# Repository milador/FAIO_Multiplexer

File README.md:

# FAIO Multiplexer Switch 

FAIO Multiplexer is an open-source Assistive technology wing for Adafruit Feather boards which enables those with limited or no hand movement to use Adaptive switches as input to operate in multiple input modes.

FAIO Multiplexer USB supports following switch modes:

* Switch Access Mode ( HID Keyboard ) : Teal Led
* Morse Keyboard Mode ( HID Keyboard ) : Purple Led
* Morse Mouse Mode ( HID Mouse ) : Pink Led
* Settings Mode : Orange Led

FAIO Multiplexer Joystick supports following switch modes:

* Mode 1 (Button 1,Button 2,Button 3,Button 4) : Teal Led
* Mode 2 (Button 5,Button 6,Button 7,Button 8) : Pink Led
* Settings Mode : Orange Led

How to change the mode?

You can change the mode by holding switch number 4 or D for 2 seconds.

Additional firmware to operate Xbox Adaptive Controller using switch module is available as well.

# Downloads 

These are all the files and documentation associated with the FAIO Multiplexer project.

 <table style="width:100%">
  <tr>
    <th>Resource</th>
    <th>Version</th>
    <th>Format</th>
    <th>Link</th>
  </tr>
    <tr>
    <td>FAIO Multiplexer All</td>
    <td>1.1</td>
    <td>ZIP</td>
    <td><a href="https://github.com/milador/FAIO_Multiplexer/archive/master.zip">FAIO_Multiplexer-master.zip</a></td>
  </tr>
  <tr>
    <td>FAIO_Multiplexer Assembly Manual</td>
    <td>Version 1.11</td>
    <td>PDF</td>
    <td><a href="https://github.com/milador/FAIO_Multiplexer/blob/master/Documentation/Build_Manuals/FAIO_Multiplexer_Instructions_Manual.pdf">FAIO_Multiplexer_Instructions_Manual.pdf</a></td>
  </tr>
   <tr>
    <td>FAIO_Multiplexer USB User Manual</td>
    <td>Version 1.1</td>
    <td>PDF</td>
    <td><a href="https://github.com/milador/FAIO_Multiplexer/blob/master/Documentation/User_Manuals/FAIO_Multiplexer_USB_User_Manual.pdf">FAIO_Multiplexer_USB_User_Manual.pdf</a></td>
  </tr>
    <tr>
    <td>FAIO_Multiplexer Joystick User Manual</td>
    <td>Version 1.1</td>
    <td>PDF</td>
    <td><a href="https://github.com/milador/FAIO_Multiplexer/blob/master/Documentation/User_Manuals/FAIO_Multiplexer_Joystick_User_Manual.pdf">FAIO_Multiplexer_Joystick_User_Manual.pdf</a></td>
  </tr>
  <tr>
    <td>FAIO_Multiplexer Switch BOM (csv)</td>
    <td>Jan 11, 2021</td>
    <td>CSV</td>
    <td><a href="https://github.com/milador/FAIO_Multiplexer/blob/master/Components/FAIO_Multiplexer_BOM.csv">FAIO_Multiplexer_BOM.csv</a></td>
  </tr>
  <tr>
    <td>FAIO_Multiplexer Switch BOM (HTML)</td>
    <td>March 12, 2021</td>
    <td>HTML</td>
    <td><a href="http://milador.ca/projects/faio_multiplexer/bom.html">bom.html</a></td>
  </tr>
  <tr>
    <td>FAIO_Multiplexer USB Switch Software</td>
    <td>1.0</td>
    <td>Ino</td>
    <td><a href="https://github.com/milador/FAIO-2/raw/master/Software/FAIO_Multiplexer_USB_Software/FAIO_Multiplexer_USB_Software.ino">FAIO_Multiplexer_USB_Software.ino</a></td>
  </tr>
  <tr>
    <td>FAIO_Multiplexer Joystick Switch Software</td>
    <td>1.0</td>
    <td>Ino</td>
    <td><a href="https://github.com/milador/FAIO-2/raw/master/Software/FAIO_Multiplexer_Joystick_Software/FAIO_Multiplexer_Joystick_Software.ino">FAIO_Multiplexer_Joystick_Software.ino</a></td>
  </tr>
  <tr>
    <td>FAIO_Multiplexer Switch Board Layout</td>
    <td>1.0</td>
    <td>BRD</td>
    <td><a href="https://raw.githubusercontent.com/milador/FAIO_Multiplexer/master/Hardware/PCB_design/FAIO_Multiplexer.brd">FAIO_Multiplexer.brd</a></td>
  </tr>
  <tr>
    <td>FAIO_Multiplexer Switch Board Schematic</td>
    <td>1.0</td>
    <td>SCH</td>
    <td><a href="https://raw.githubusercontent.com/milador/FAIO_Multiplexer/master/Hardware/PCB_design/FAIO_Multiplexer.sch">FAIO_Multiplexer.sch</a></td>
  </tr>
   <tr>
    <td>FAIO_Multiplexer Battery Holder enclosure</td>
    <td>1.1</td>
    <td>STL</td>
    <td><a href="https://github.com/milador/FAIO_Multiplexer/blob/master/Hardware/Housing_design/STL/FAIO_Multiplexer_Body_Battery_Holder.stl">FAIO_Multiplexer_Body_Battery_Holder.stl</a></td>
  </tr>
  <tr>
    <td>FAIO_Multiplexer Bottom enclosure</td>
    <td>1.1</td>
    <td>STL</td>
    <td><a href="https://github.com/milador/FAIO_Multiplexer/blob/master/Hardware/Housing_design/STL/FAIO_Multiplexer_Body_Bottom.stl">FAIO_Multiplexer_Body_Bottom.stl</a></td>
  </tr>
  <tr>
    <td>FAIO_Multiplexer Bottom enclosure with camera mount threaded screw hole</td>
    <td>1.1</td>
    <td>STL</td>
    <td><a href="https://github.com/milador/FAIO_Multiplexer/blob/master/Hardware/Housing_design/STL/FAIO_Multiplexer_Body_Bottom_With_Mount.stl">FAIO_Multiplexer_Body_Bottom_With_Mount.stl</a></td>
  </tr>
  <tr>
    <td>FAIO_Multiplexer Top enclosure</td>
    <td>1.1</td>
    <td>STL</td>
    <td><a href="https://github.com/milador/FAIO_Multiplexer/blob/master/Hardware/Housing_design/STL/FAIO_Multiplexer_Body_Top.stl">FAIO_Multiplexer_Body_Top.stl</a></td>
  </tr>
</table> 

# Usage

The FAIO Multiplexer switch interface can operate in 4 modes and switch D is used to switch between them.The RGB Led blinks 2 times to indicate the current mode.

## USB or Bluetooth Switch mode

 <table style="width:100%">
  <tr>
    <th>Mode Number</th>
    <th>Mode</th>
    <th>Color</th>
  </tr>
    <tr>
    <td>1</td>
    <td>Keyboard Switch</td>
    <td>Teal</td>
  </tr>
  <tr>
    <td>2</td>
    <td>Morse Keyboard</td>
    <td>Purple</td>
  </tr>
  <tr>
    <td>3</td>
    <td>Morse Mouse</td>
    <td>Pink</td>
  </tr>
  <tr>
    <td>4</td>
    <td>Settings</td>
    <td>Orange</td>
  </tr>
</table> 

## Joystick Switch mode

 <table style="width:100%">
  <tr>
    <th>Joystick Button Number (Mode 1,Mode 2)</th>
    <th>Xbox Button</th>
    <th>Color</th>
  </tr>
    <tr>
    <td>(1,5)</td>
    <td>X1</td>
    <td>Blue</td>
  </tr>
  <tr>
    <td>(2,6)</td>
    <td>X2</td>
    <td>Yellow</td>
  </tr>
  <tr>
    <td>(3,7)</td>
    <td>A</td>
    <td>Green</td>
  </tr>
  <tr>
    <td>(4,8)</td>
    <td>B</td>
    <td>Red</td>
  </tr>
</table> 

## Software Setup Instructions

  1. Install the required libraries 
  
  1.1. Install Neo Pixels : https://github.com/adafruit/Adafruit_NeoPixel

  1.2. Install EasyMorse if using USB or Bluetooth version : https://github.com/milador/EasyMorse
  
  1.3. Install StopWatch if using USB or Bluetooth version : https://github.com/RobTillaart/Arduino/tree/master/libraries/StopWatch
  
  1.4. Install FlashStorage if using Feather M0 Board : https://github.com/cmaglie/FlashStorage

  1.5. Install Joystick library: https://github.com/MHeironimus/ArduinoJoystickLibrary or https://github.com/gdsports/ArduinoJoystickLibrary/tree/samd_patch
  
  2. Download the firmware 
  
  2.1. USB Firmware : https://github.com/milador/FAIO_Multiplexer/raw/master/Software/FAIO_Multiplexer_USB_Software/FAIO_Multiplexer_USB_Software.ino

  2.2. Joystick Firmware : https://github.com/milador/FAIO_Multiplexer/raw/master/Software/FAIO_Multiplexer_Joystick_Software/FAIO_Multiplexer_Joystick_Software.ino
  
  2.3. Bluetooth Firmware (Coming up)
  
  3. Setup Arduino IDE for your feather board according to the instructions on Adafruit website
  
  4. Verify and upload firmware code to your Feather Board

# License

## Creative Commons Attribution-NonCommercial-ShareAlike (CC-BY-NC-SA)

Copyright (c) 2018 Milador

A creative commons license that bans commercial use and requires you to release any modified works under this license.

<br />This work is licensed under a <a rel="license" href="http://creativecommons.org/licenses/by-nc-sa/3.0/">Creative Commons Attribution-NonCommercial-ShareAlike 3.0 Unported License</a>.

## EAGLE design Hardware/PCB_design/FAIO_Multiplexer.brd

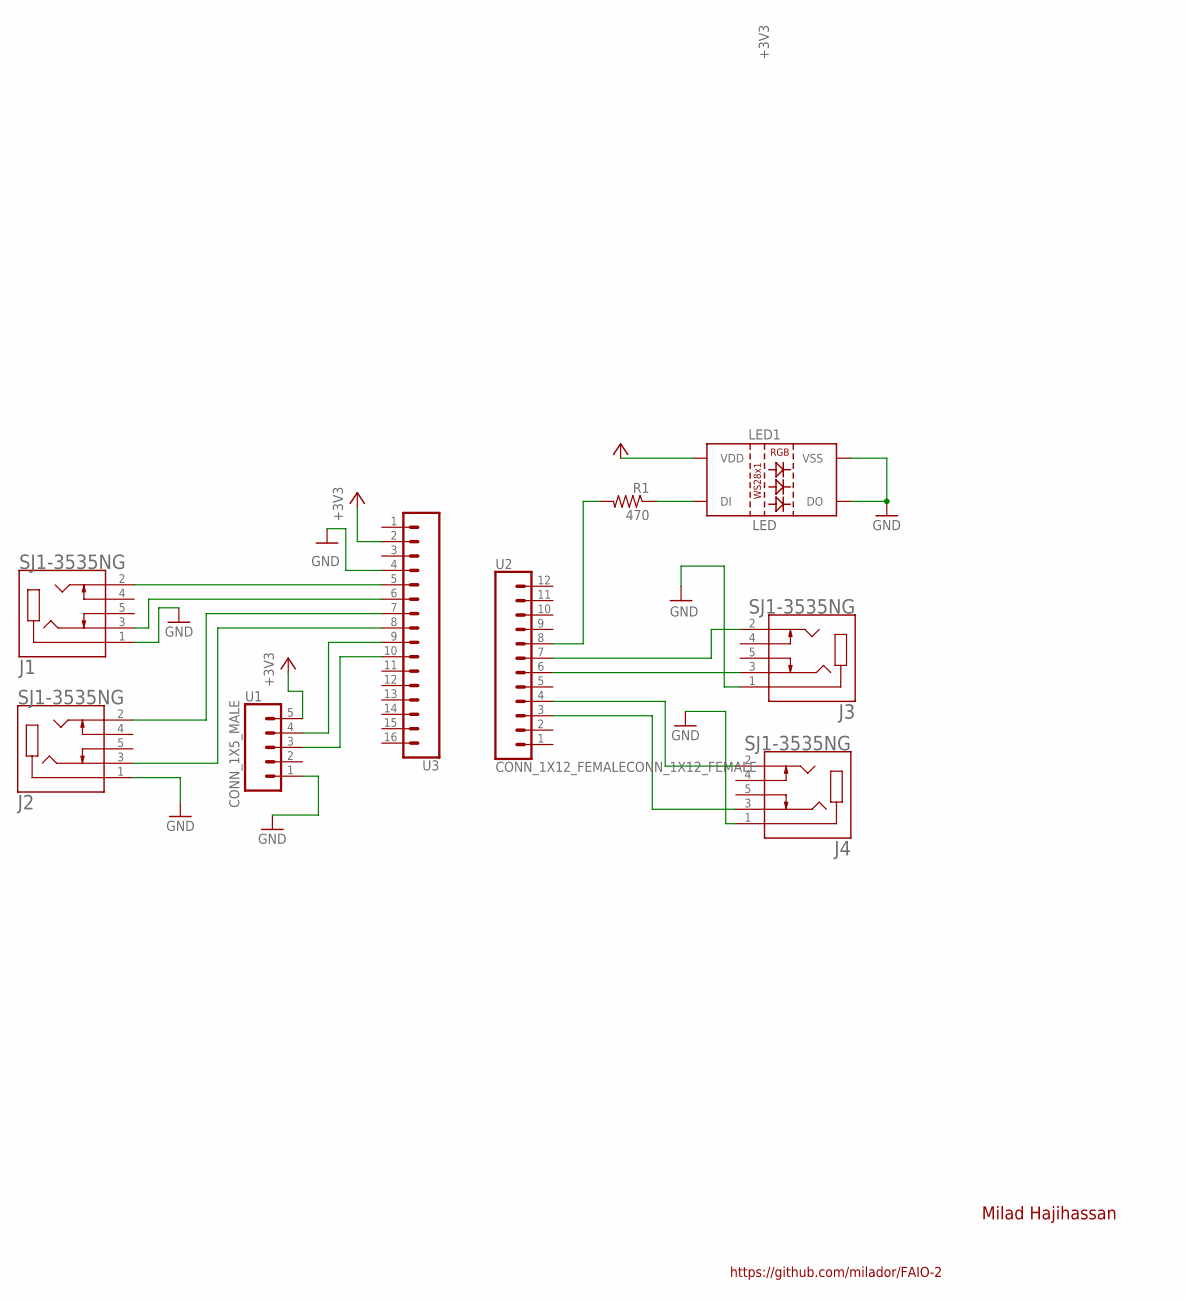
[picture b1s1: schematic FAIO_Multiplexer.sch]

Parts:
J1, J2, J3, J4: SJ1-3535NG; CUI_SJ1-3535NG
LED1: LED; NEOPIXELS-5MM
R1: 470; 0204/7
U1: CONN_1X5_MALE; CONN_1X5
U2: CONN_1X12_FEMALECONN_1X12_FEMALE; CONN_1X12
U3: CONN_1X16_FEMALECONN_1X16_FEMALE; CONN_1X16

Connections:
+3V3: LED1.2 (VDD), U1.5, U3.2
GND: J1.1, J2.1, J3.1, J4.1, LED1.3 (VSS), LED1.4 (DO), U1.1, U3.4
unnamed: J3.3, U2.6
unnamed: J3.2, U2.7
unnamed: J4.2, U2.4
unnamed: LED1.1 (DI), R1.1
unnamed: J4.3, U2.3
unnamed: R1.2, U2.8
unnamed: U1.4, U3.9
unnamed: J1.2, U3.5
unnamed: J1.3, U3.6
unnamed: J2.2, U3.7
unnamed: U1.3, U3.10
unnamed: J2.3, U3.8

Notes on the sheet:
https://github.com/milador/FAIO-2
Milad Hajihassan

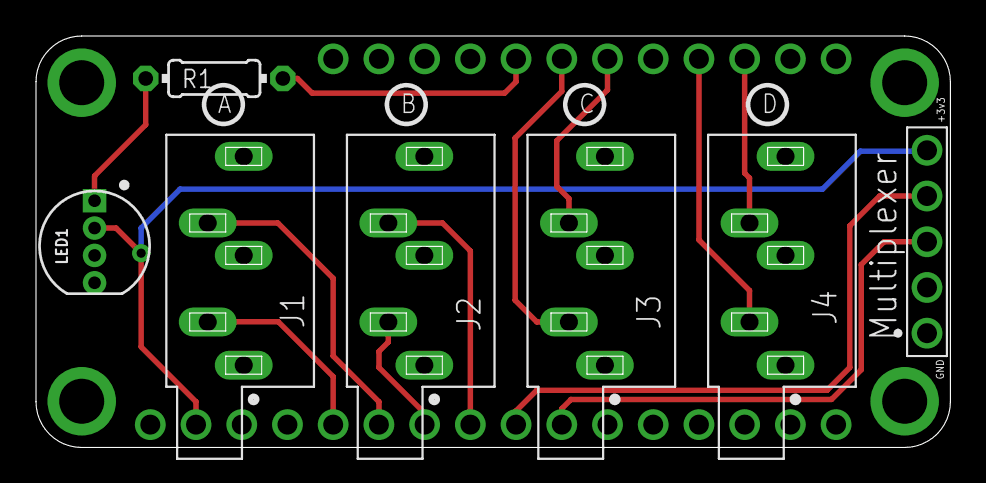
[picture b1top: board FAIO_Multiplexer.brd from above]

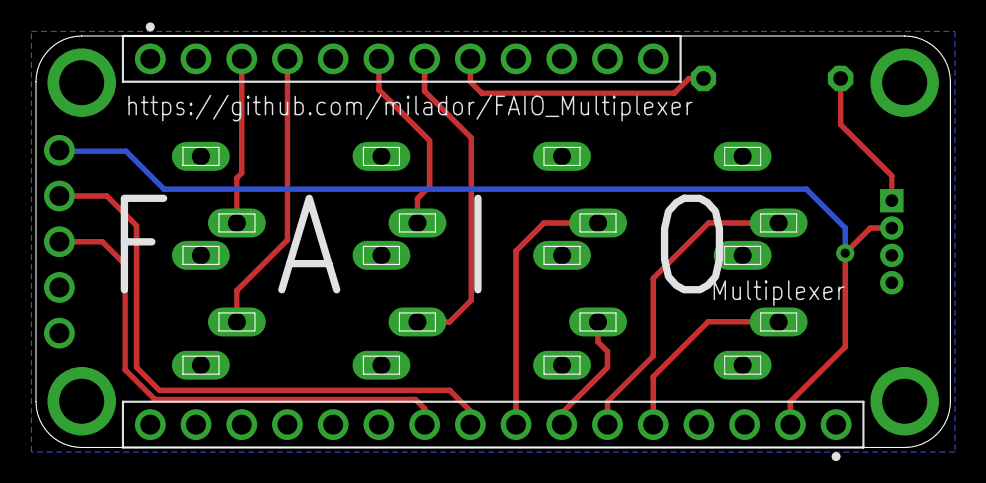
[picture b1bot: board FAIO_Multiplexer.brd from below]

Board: 2 copper layers, 50.8 x 22.9 mm, 9 parts (2 on the bottom side), 14 nets.

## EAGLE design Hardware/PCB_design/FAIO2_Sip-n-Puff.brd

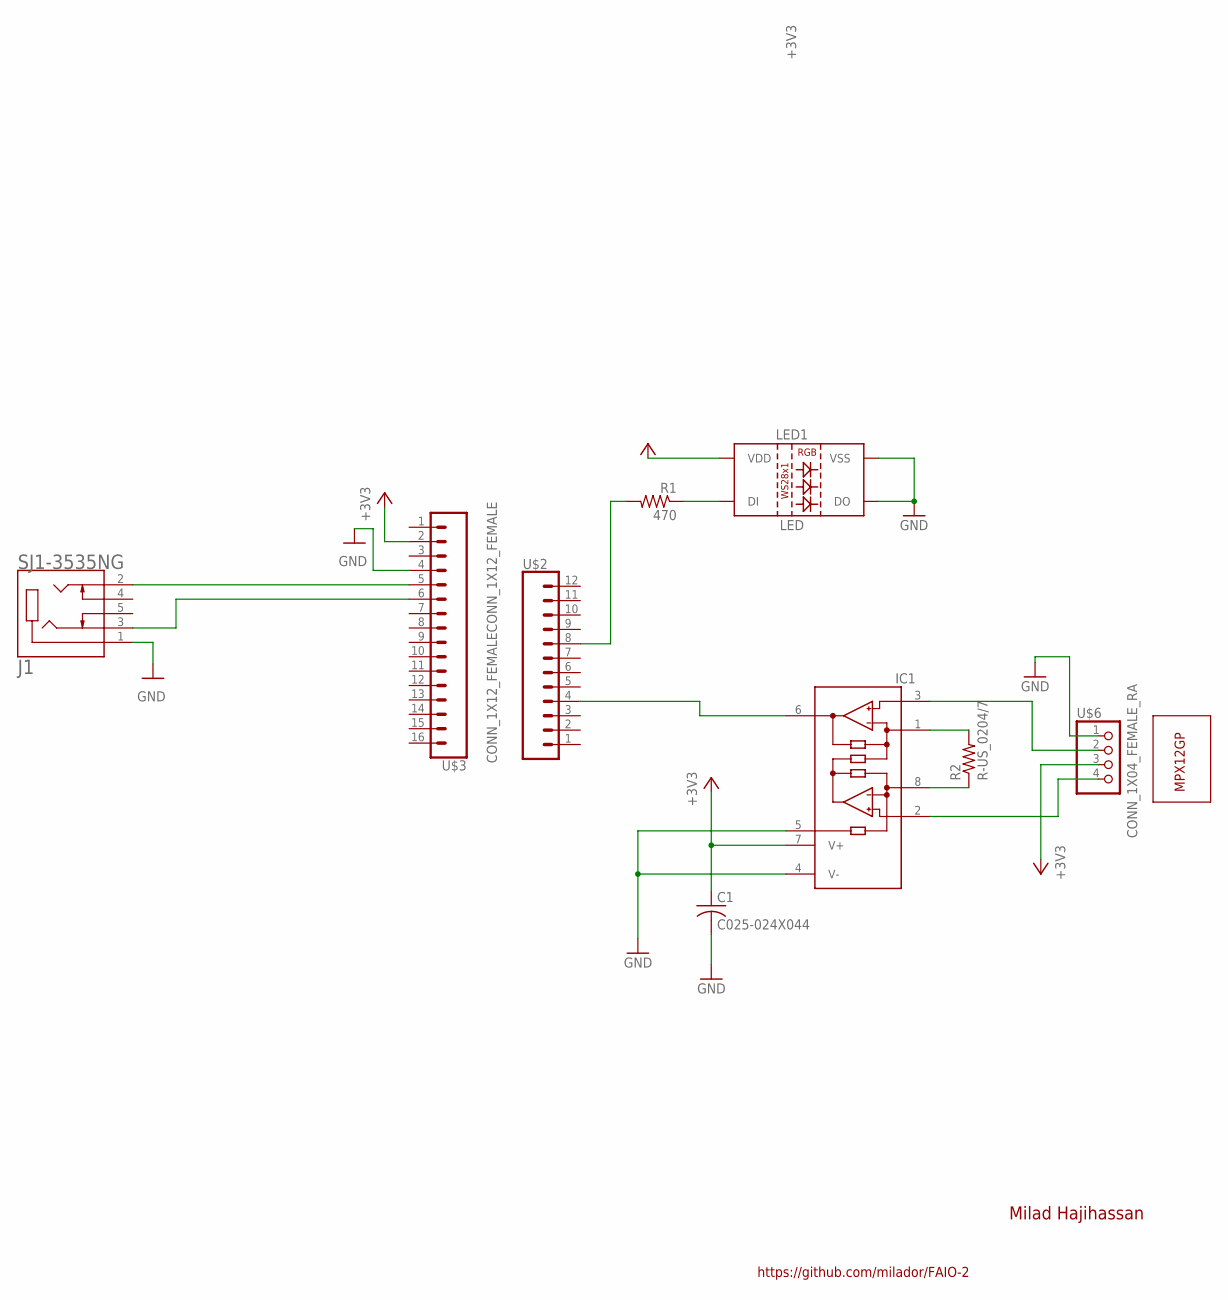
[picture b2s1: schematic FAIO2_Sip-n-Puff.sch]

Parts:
C1: C025-024X044
IC1: INA122PDIL08; DIL08
J1: SJ1-3535NG; CUI_SJ1-3535NG
LED1: LED; NEOPIXELS-5MM
R1: 470; 0204/7
R2: R-US_0204/7; 0204/7
U$1: MPX12GPMPX12GP; MPX
U$2: CONN_1X12_FEMALECONN_1X12_FEMALE; CONN_1X12
U$3: CONN_1X16_FEMALECONN_1X16_FEMALE; CONN_1X16
U$6: CONN_1X04_FEMALE_RA; HDRRAR4W64P254_1X4_1066X850X254B

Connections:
+3V3: C1.1, IC1.7 (V+), LED1.2 (VDD), U$3.2, U$6.3
GND: C1.2, IC1.4 (V-), IC1.5 (REF), J1.1, LED1.3 (VSS), LED1.4 (DO), U$3.4, U$6.1
unnamed: IC1.6 (OUT), U$2.4
unnamed: LED1.1 (DI), R1.1
unnamed: IC1.1 (RG), R2.2
unnamed: R1.2, U$2.8
unnamed: J1.2, U$3.5
unnamed: J1.3, U$3.6
unnamed: IC1.8 (RG), R2.1
unnamed: IC1.3 (+IN), U$6.2
unnamed: IC1.2 (-IN), U$6.4

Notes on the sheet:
https://github.com/milador/FAIO-2
Milad Hajihassan

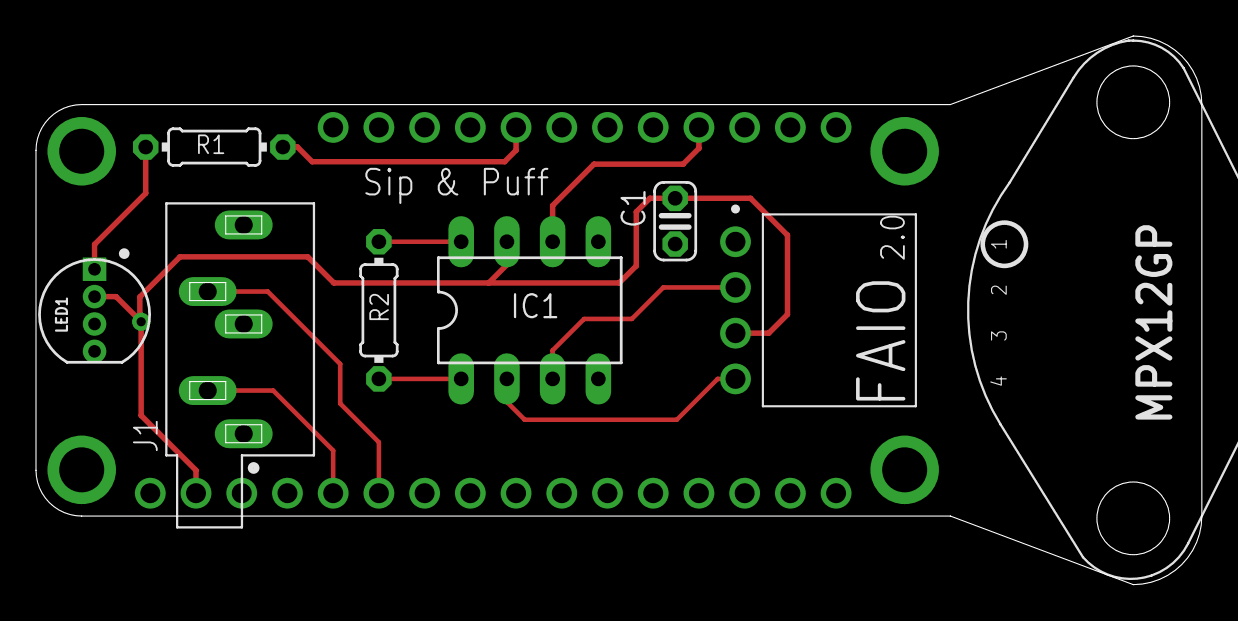
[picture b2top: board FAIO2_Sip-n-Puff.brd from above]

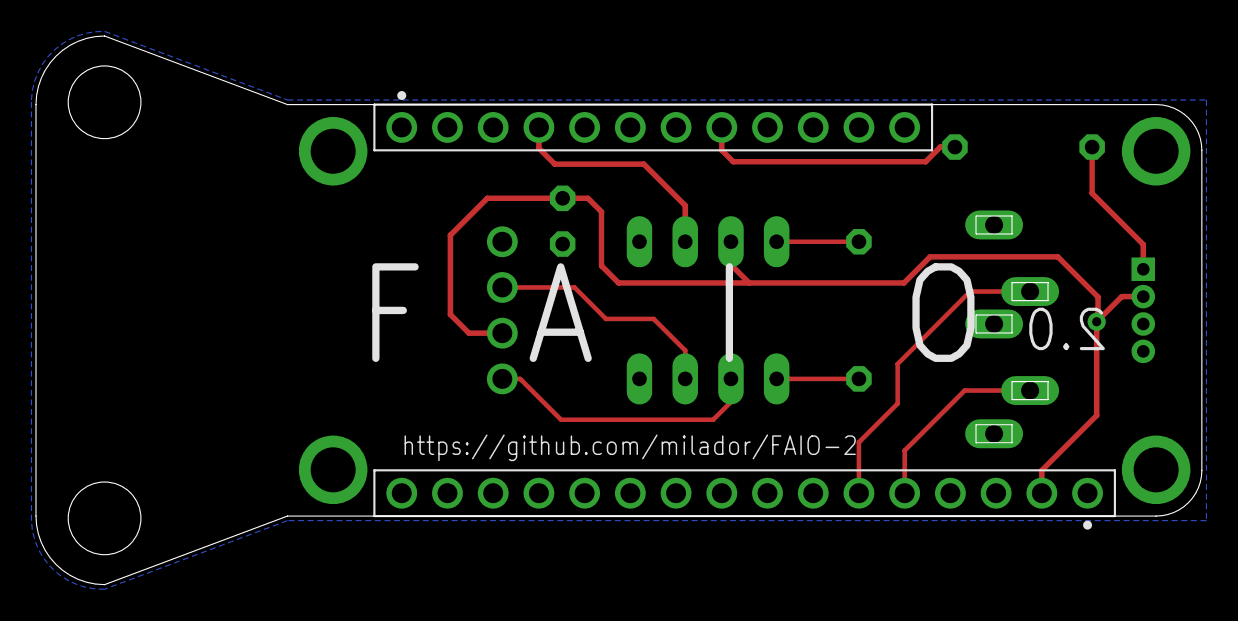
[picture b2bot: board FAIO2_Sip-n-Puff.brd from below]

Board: 2 copper layers, 64.8 x 30.5 mm, 10 parts (2 on the bottom side), 11 nets.

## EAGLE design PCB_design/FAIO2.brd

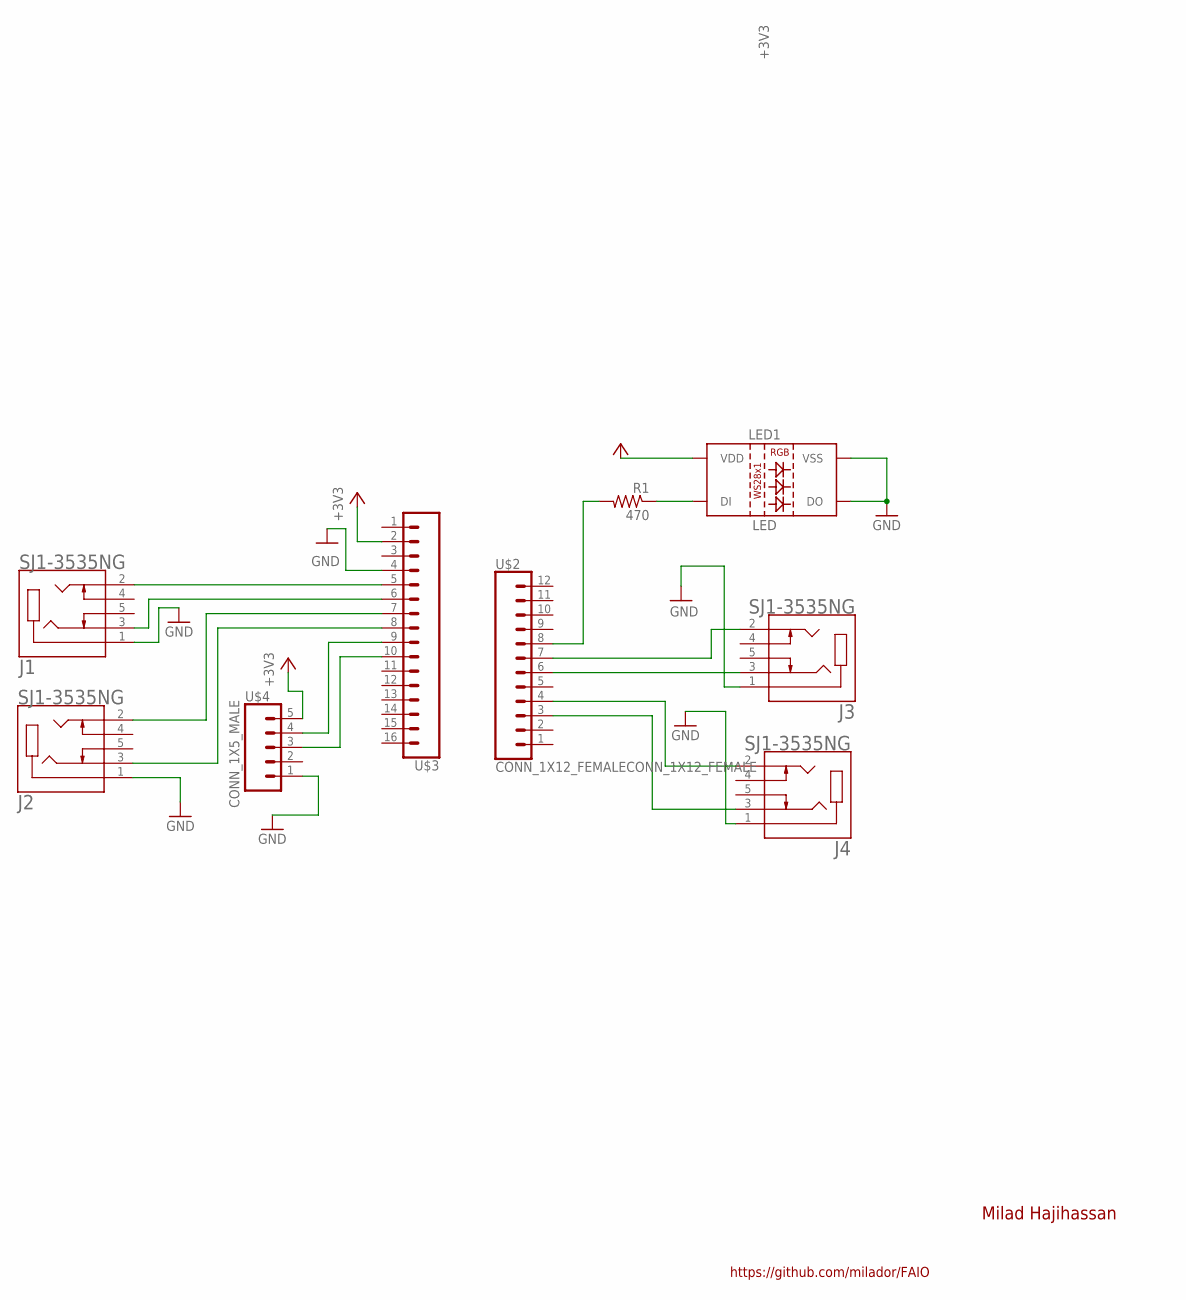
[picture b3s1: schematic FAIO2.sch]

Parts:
J1, J2, J3, J4: SJ1-3535NG; CUI_SJ1-3535NG
LED1: LED; NEOPIXELS-5MM
R1: 470; 0204/7
U$2: CONN_1X12_FEMALECONN_1X12_FEMALE; CONN_1X12
U$3: CONN_1X16_FEMALECONN_1X16_FEMALE; CONN_1X16
U$4: CONN_1X5_MALE; CONN_1X5

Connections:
+3V3: LED1.2 (VDD), U$3.2, U$4.5
GND: J1.1, J2.1, J3.1, J4.1, LED1.3 (VSS), LED1.4 (DO), U$3.4, U$4.1
unnamed: J3.3, U$2.6
unnamed: J3.2, U$2.7
unnamed: J4.2, U$2.4
unnamed: LED1.1 (DI), R1.1
unnamed: J4.3, U$2.3
unnamed: R1.2, U$2.8
unnamed: U$3.9, U$4.4
unnamed: J1.2, U$3.5
unnamed: J1.3, U$3.6
unnamed: J2.2, U$3.7
unnamed: U$3.10, U$4.3
unnamed: J2.3, U$3.8

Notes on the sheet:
https://github.com/milador/FAIO
Milad Hajihassan

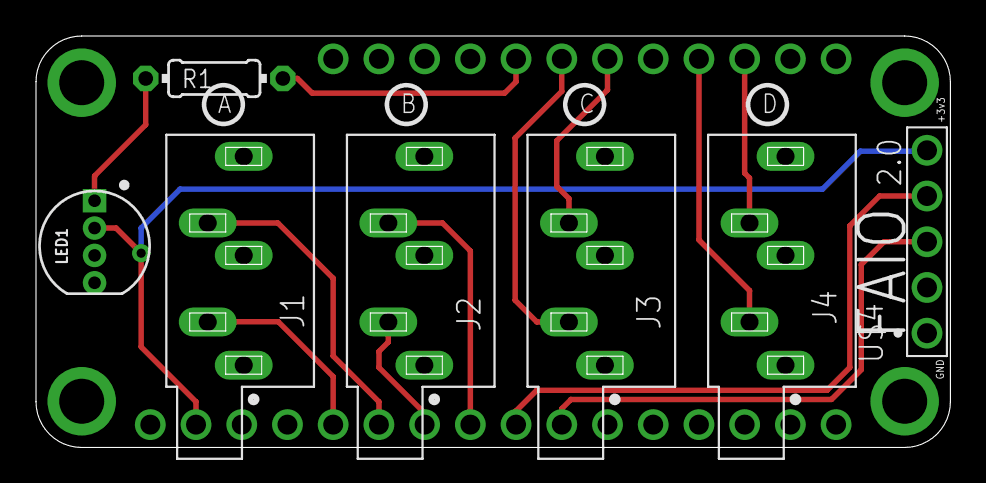
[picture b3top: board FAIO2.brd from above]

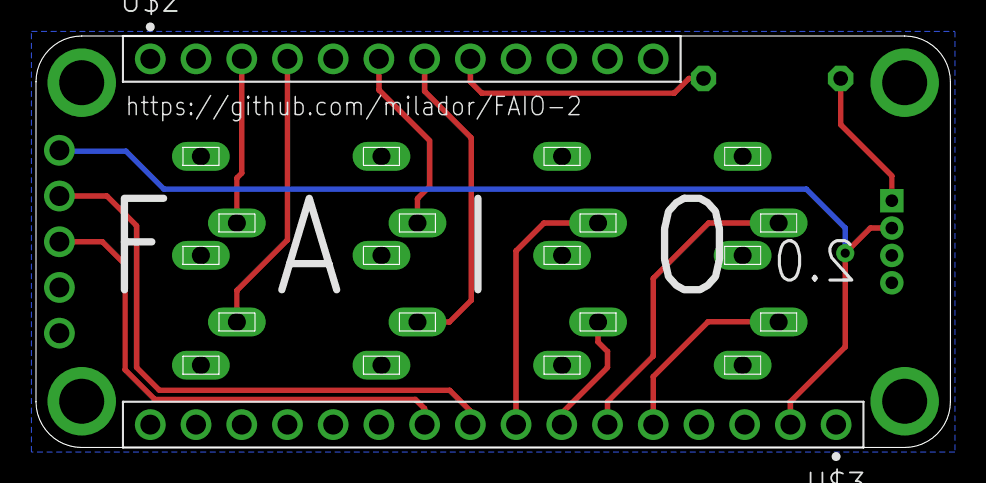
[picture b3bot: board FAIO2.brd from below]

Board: 2 copper layers, 50.8 x 22.9 mm, 9 parts (2 on the bottom side), 14 nets.

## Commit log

2019-02-04 Added USB Mode and XAC Joystick mode firmware
2019-02-19 Added the PCB Files.
2019-02-19 Moved PCB files
2019-02-19 Added images
2019-02-19 Moved the PCB files
2019-02-19 Added BOM file
2019-02-22 no message
2019-02-24 CSV version of BOM
2019-02-25 Changed naming convention
2019-02-26 Added Sip and puff module PCB files
2019-02-26 Updated BOM Files
2019-02-27 Fixed the bugs for Atmega32U4
2019-04-20 Changed FAIO project github page to two separate projects
2019-04-20 Changed BOM file name
2019-04-21 Corrected resistor value
2019-09-30 Added the enclosure STL files and the instructions manual
2019-09-30 Added manual version number
2019-10-05 Updated the Manual.
2020-04-13 Updated firmware
2020-04-13 Added user manuals
2020-04-13 New stl files
2020-04-13 Update README.md
    Added links to user manuals
2020-07-24 Updated code: Fixed typo in description, Removed Wireless BOM file
2020-07-25 Updated readme file
2020-09-29 Added design overview diagrams
2020-11-29 Updated STL files
2020-11-29 Removed untested files
2020-12-20 Updated BOM and added M2.5 screws
2021-01-11 Updated BOM file for the new enclosure
2021-01-11 Update Manuals for the new enclosure
2021-01-11 Updated enclosure files : New snap fit enclosure
2021-01-11 Updated Manual - Corrected spacing
2021-01-12 Updated enclosure file links
2021-01-12 Updated enclosure STL files (2.7mm holder holes)
2021-01-12 Added 3D model images
2021-01-12 Added 3D model images to readme
2021-01-17 Updated Enclosure : Snap wall height was increased by 0.8mm.
2021-01-17 Updated STL Links
2021-01-18 Updated Manuals : Updated enclosure images
2021-01-18 Updated images
2021-01-18 Moved manuals to new directory.
2021-01-18 Directory corrected
2021-01-18 Updated links
2021-01-18 Added PCB gerber files
2021-01-31 Updated Assembly manual 1.11
2021-02-25 Added License text
2021-02-26 Updated license
    Attribution-NonCommercial-ShareAlike 3.0 Unported (CC BY-NC-SA 3.0)
2021-02-26 License
2021-02-26 Update LICENSE
2021-02-26 Added CP code
2021-03-13 Updated PCB Files: 2.0 text changed to Multiplexer
2021-03-13 HTML BOM File added

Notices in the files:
parts and their libraries:
SparkFun-Aesthetics: Licensing: CC v3.0 Share-Alike You are welcome to use this library for commercial purposes.
